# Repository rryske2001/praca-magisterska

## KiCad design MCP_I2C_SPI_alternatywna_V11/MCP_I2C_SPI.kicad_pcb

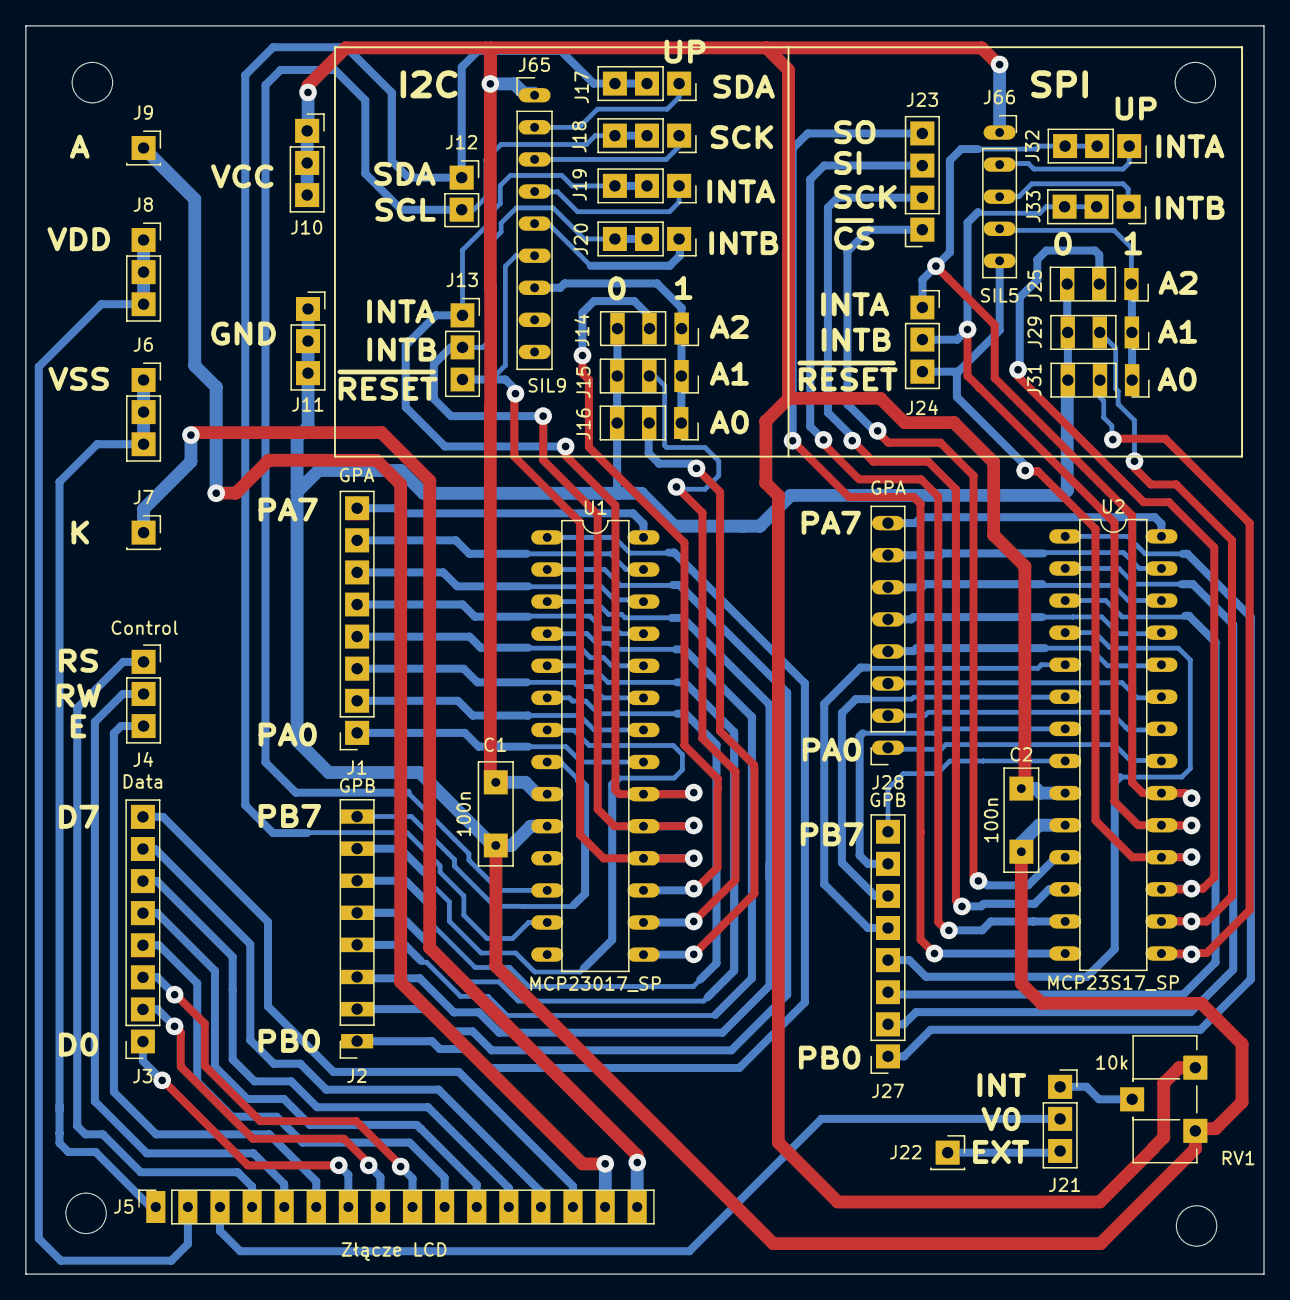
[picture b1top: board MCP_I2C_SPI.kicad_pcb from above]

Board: 2 copper layers, 98.0 x 98.8 mm, 38 parts (0 on the bottom side), 78 nets.

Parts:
C1, C2: 100n; C_Disc_D8.0mm_W2.5mm_P5.00mm_kwadart
J1, J28: GPA; PinSocket_1x08_P2.54mm_Vertical_kwadrat
J2, J27: GPB; PinSocket_1x08_P2.54mm_Vertical_kwadrat
J3: Data; PinSocket_1x08_P2.54mm_Vertical_kwadrat
J4: Control; PinSocket_1x03_P2.54mm_Vertical
J5: Złącze LCD; PinSocket_1x16_P2.54mm_Vertical_kwadrat
J6: VSS; PinSocket_1x03_P2.54mm_Vertical
J7: K; PinSocket_1x01_P2.54mm_Vertical_kwadart
J8: VDD; PinSocket_1x03_P2.54mm_Vertical
J9: A; PinSocket_1x01_P2.54mm_Vertical_kwadart
J10: VCC; PinSocket_1x03_P2.54mm_Vertical
J11: GND; PinSocket_1x03_P2.54mm_Vertical
J12: I2C; PinSocket_1x02_P2.54mm_Vertical_square
J13: Interrupt0; PinSocket_1x03_P2.54mm_Vertical
J14, J25: A2; PinSocket_1x03_P2.54mm_Vertical
J15, J29: A1; PinSocket_1x03_P2.54mm_Vertical
J16, J31: A0; PinSocket_1x03_P2.54mm_Vertical
J17: SDA; PinSocket_1x03_P2.54mm_Vertical
J18: SCK; PinSocket_1x03_P2.54mm_Vertical
J19, J32: INTA; PinSocket_1x03_P2.54mm_Vertical
J20, J33: INTB; PinSocket_1x03_P2.54mm_Vertical
J21: V0; PinSocket_1x03_P2.54mm_Vertical
J22: EXT; PinSocket_1x01_P2.54mm_Vertical_kwadart
J23: SPI; PinSocket_1x04_P2.54mm_Vertical
J24: InterruptS; PinSocket_1x03_P2.54mm_Vertical
J65: SIL9; PinHeader_1x09_P2.54mm_Vertical
J66: SIL5; PinSocket_1x05_P2.54mm_Vertical
RV1: 10k; Potentiometer_ACP_CA9-H5_Horizontal_kwadrat
U1: MCP23017_SP; DIP-28_W7.62mm
U2: MCP23S17_SP; DIP-28_W7.62mm

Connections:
+5V: C1.1, C2.1, J10.1, J10.2, J10.3, J65.1, J66.1, RV1.3, U1.9 (VDD), U2.9 (VDD)
CS: J23.1, U2.11 (~CS)
GND: C1.2, C2.2, J11.1, J11.2, J11.3, J14.3, J15.3, J16.3, J25.3, J29.3, J31.3, RV1.1, U1.10 (VSS), U2.10 (VSS)
INTA0: J13.1, J19.2, J19.3, U1.20 (INTA)
INTAS: J24.1, J32.2, J32.3, U2.20 (INTA)
INTB0: J13.2, J20.2, J20.3, U1.19 (INTB)
INTBS: J24.2, J33.2, J33.3, U2.19 (INTB)
unnamed: J1.1, U1.21 (GPA0)
unnamed: J1.2, U1.22 (GPA1)
unnamed: J1.3, U1.23 (GPA2)
unnamed: J1.4, U1.24 (GPA3)
unnamed: J1.5, U1.25 (GPA4)
unnamed: J1.6, U1.26 (GPA5)
unnamed: J1.7, U1.27 (GPA6)
unnamed: J1.8, U1.28 (GPA7)
unnamed: J2.1, U1.1 (GPB0)
unnamed: J2.2, U1.2 (GPB1)
unnamed: J2.3, U1.3 (GPB2)
unnamed: J2.4, U1.4 (GPB3)
unnamed: J2.5, U1.5 (GPB4)
unnamed: J2.6, U1.6 (GPB5)
unnamed: J2.7, U1.7 (GPB6)
unnamed: J2.8, U1.8 (GPB7)
unnamed: J3.1, J5.7
unnamed: J3.2, J5.8
unnamed: J3.3, J5.9
unnamed: J3.4, J5.10
unnamed: J3.5, J5.11
unnamed: J3.6, J5.12
unnamed: J3.7, J5.13
unnamed: J3.8, J5.14
unnamed: J4.1, J5.4
unnamed: J4.2, J5.5
unnamed: J4.3, J5.6
unnamed: J5.1, J6.1, J6.2, J6.3
unnamed: J5.2, J8.1, J8.2, J8.3
unnamed: J5.15, J9.1
unnamed: J5.16, J7.1
unnamed: J14.1, J15.1, J16.1, J65.7
unnamed: J14.2, U1.17 (A2)
unnamed: J15.2, U1.16 (A1)
unnamed: J16.2, U1.15 (A0)
unnamed: J17.1, J65.2
unnamed: J18.1, J65.3
unnamed: J19.1, J65.4
unnamed: J20.1, J65.5
unnamed: J21.1, RV1.2
unnamed: J5.3, J21.2
unnamed: J21.3, J22.1
unnamed: J25.1, J29.1, J31.1, J66.4
unnamed: J25.2, U2.17 (A2)
unnamed: J27.1, U2.1 (GPB0)
unnamed: J27.2, U2.2 (GPB1)
unnamed: J27.3, U2.3 (GPB2)
unnamed: J27.4, U2.4 (GPB3)
unnamed: J27.5, U2.5 (GPB4)
unnamed: J27.6, U2.6 (GPB5)
unnamed: J27.7, U2.7 (GPB6)
unnamed: J27.8, U2.8 (GPB7)
unnamed: J28.1, U2.21 (GPA0)
unnamed: J28.2, U2.22 (GPA1)
unnamed: J28.3, U2.23 (GPA2)
unnamed: J28.4, U2.24 (GPA3)
unnamed: J28.5, U2.25 (GPA4)
unnamed: J28.6, U2.26 (GPA5)
unnamed: J28.7, U2.27 (GPA6)
unnamed: J28.8, U2.28 (GPA7)
unnamed: J29.2, U2.16 (A1)
unnamed: J31.2, U2.15 (A0)
unnamed: J32.1, J66.2
unnamed: J33.1, J66.3
RESET0: J13.3, J65.6, U1.18 (~RESET)
RESETS: J24.3, J66.5, U2.18 (~RESET)
SCK: J23.2, U2.12 (SCK)
SCL: J12.2, J18.2, J18.3, U1.12 (SCK)
SDA: J12.1, J17.2, J17.3, U1.13 (SDA)
SI: J23.3, U2.13 (SI)
SO: J23.4, U2.14 (SO)

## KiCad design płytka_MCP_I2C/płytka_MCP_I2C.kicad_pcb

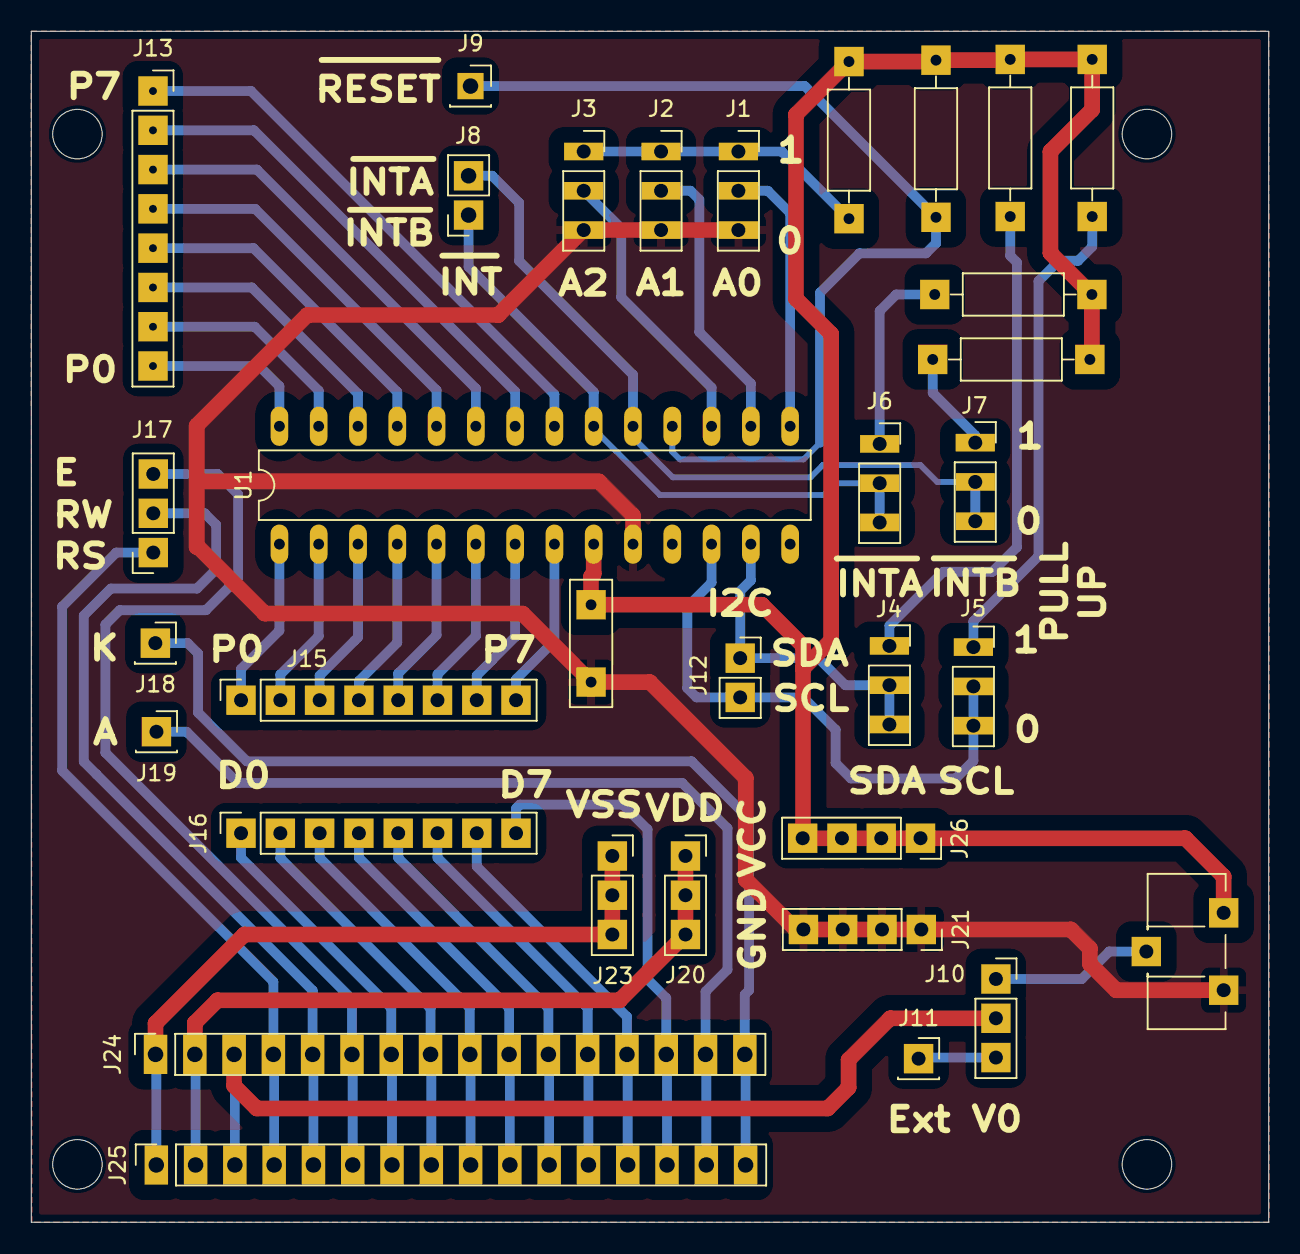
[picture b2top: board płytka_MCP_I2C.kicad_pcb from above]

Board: 2 copper layers, 80.0 x 77.0 mm, 33 parts (0 on the bottom side), 49 nets.

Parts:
C1: 47n; C_Disc_D8.0mm_W2.5mm_P5.00mm_kwadart
J1: A0; PinSocket_1x03_P2.54mm_Vertical
J2: A1; PinSocket_1x03_P2.54mm_Vertical
J3: A2; PinSocket_1x03_P2.54mm_Vertical
J4: SDA; PinSocket_1x03_P2.54mm_Vertical
J5: SCL; PinSocket_1x03_P2.54mm_Vertical
J6: INTA; PinSocket_1x03_P2.54mm_Vertical
J7: INTB; PinSocket_1x03_P2.54mm_Vertical
J8: INTA; PinSocket_1x02_P2.54mm_Vertical
J9: RESET; PinSocket_1x01_P2.54mm_Vertical
J10: V0; PinSocket_1x03_P2.54mm_Vertical
J11: Ext; PinSocket_1x01_P2.54mm_Vertical
J12: I2C; PinSocket_1x02_P2.54mm_Vertical
J13, J15: U2; PinSocket_1x08_P2.54mm_Vertical_kwadrat
J16: U3; PinSocket_1x08_P2.54mm_Vertical
J17: RS; PinSocket_1x03_P2.54mm_Vertical
J18: K; PinSocket_1x01_P2.54mm_Vertical_kwadart
J19: A; PinSocket_1x01_P2.54mm_Vertical_kwadart
J20: VDD; PinSocket_1x03_P2.54mm_Vertical
J21: GND; PinSocket_1x04_P2.54mm_Vertical
J23: VSS; PinSocket_1x03_P2.54mm_Vertical
J24: Conn_01x16_Pin; PinSocket_1x16_P2.54mm_Vertical_kwadrat
J25: LCD; PinSocket_1x16_P2.54mm_Vertical_kwadrat
J26: VCC; PinSocket_1x04_P2.54mm_Vertical
R1, R4, R5, R6: 10k; R_Axial_DIN0207_L6.3mm_D2.5mm_P10.16mm_Horizontal_square
R2, R3: 4.7k; R_Axial_DIN0207_L6.3mm_D2.5mm_P10.16mm_Horizontal_square
RV1: 10k; Potentiometer_ACP_CA9-H5_Horizontal_kwadrat
U1: MCP23017_SP; DIP-28_W7.62mm_LongPads_Edit

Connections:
GND: C1.1, J1.3, J2.3, J3.3, J21.1, J21.2, J21.3, J21.4, RV1.1, U1.10 (VSS)
unnamed: J1.1, J2.1, J3.1, R1.2
unnamed: J1.2, U1.15 (A0)
unnamed: J2.2, U1.16 (A1)
unnamed: J3.2, U1.17 (A2)
unnamed: J4.1, R2.2
unnamed: J5.1, R3.2
unnamed: J6.1, R4.2
unnamed: J6.2, J6.3, J8.1, U1.20 (INTA)
unnamed: J7.1, R5.2
unnamed: J7.2, J7.3, J8.2, U1.19 (INTB)
unnamed: J9.1, R6.1, U1.18 (~RESET)
unnamed: J10.1, RV1.2
unnamed: J10.2, J24.3, J25.3
unnamed: J10.3, J11.1
unnamed: J4.2, J4.3, J12.1, U1.13 (SDA)
unnamed: J5.2, J5.3, J12.2, U1.12 (SCK)
unnamed: J13.1, U1.21 (GPA0)
unnamed: J13.2, U1.22 (GPA1)
unnamed: J13.3, U1.23 (GPA2)
unnamed: J13.4, U1.24 (GPA3)
unnamed: J13.5, U1.25 (GPA4)
unnamed: J13.6, U1.26 (GPA5)
unnamed: J13.7, U1.27 (GPA6)
unnamed: J13.8, U1.28 (GPA7)
unnamed: J15.1, U1.1 (GPB0)
unnamed: J15.2, U1.2 (GPB1)
unnamed: J15.3, U1.3 (GPB2)
unnamed: J15.4, U1.4 (GPB3)
unnamed: J15.5, U1.5 (GPB4)
unnamed: J15.6, U1.6 (GPB5)
unnamed: J15.7, U1.7 (GPB6)
unnamed: J15.8, U1.8 (GPB7)
unnamed: J16.1, J24.7, J25.7
unnamed: J16.2, J24.8, J25.8
unnamed: J16.3, J24.9, J25.9
unnamed: J16.4, J24.10, J25.10
unnamed: J16.5, J24.11, J25.11
unnamed: J16.6, J24.12, J25.12
unnamed: J16.7, J24.13, J25.13
unnamed: J16.8, J24.14, J25.14
unnamed: J17.1, J24.4, J25.4
unnamed: J17.2, J24.5, J25.5
unnamed: J17.3, J24.6, J25.6
unnamed: J18.1, J24.16, J25.16
unnamed: J19.1, J24.15, J25.15
unnamed: J20.1, J20.2, J20.3, J24.2, J25.2
unnamed: J23.1, J23.2, J23.3, J24.1, J25.1
VCC: C1.2, J26.1, J26.2, J26.3, J26.4, R1.1, R2.1, R3.1, R4.1, R5.1, R6.2, RV1.3, U1.9 (VDD)

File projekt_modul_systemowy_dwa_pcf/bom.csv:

"Reference","Value","Datasheet","Footprint","Qty","DNP"
"C1,C2","47n","~","Library:C_Disc_D8.0mm_W2.5mm_P5.00mm_kwadart","2",""
"J1,J9","A0","~","Library:PinSocket_1x03_P2.54mm_Vertical","2",""
"J2,J8","A1","~","Library:PinSocket_1x03_P2.54mm_Vertical","2",""
"J3,J7","A2","~","Library:PinSocket_1x03_P2.54mm_Vertical","2",""
"J4","SDA","~","Library:PinSocket_1x03_P2.54mm_Vertical","1",""
"J5","SCL","~","Library:PinSocket_1x03_P2.54mm_Vertical","1",""
"J6,J13","INT","~","Connector_PinSocket_2.54mm:PinSocket_1x01_P2.54mm_Vertical,Library:PinSocket_1x03_P2.54mm_Vertical","2",""
"J10","V0","~","Library:PinSocket_1x03_P2.54mm_Vertical","1",""
"J11","Ext","~","Connector_PinSocket_2.54mm:PinSocket_1x01_P2.54mm_Vertical","1",""
"J12","I2C","~","Connector_PinSocket_2.54mm:PinSocket_1x02_P2.54mm_Vertical","1",""
"J14","U1","~","Library:PinSocket_1x03_P2.54mm_Vertical","1",""
"J15","U2","~","Library:PinSocket_1x08_P2.54mm_Vertical_kwadrat","1",""
"J16","U3","~","Connector_PinSocket_2.54mm:PinSocket_1x08_P2.54mm_Vertical","1",""
"J17","RS","~","Connector_PinSocket_2.54mm:PinSocket_1x03_P2.54mm_Vertical","1",""
"J18","K","~","Library:PinSocket_1x01_P2.54mm_Vertical_kwadart","1",""
"J19","A","~","Library:PinSocket_1x01_P2.54mm_Vertical_kwadart","1",""
"J20","VDD","~","Connector_PinSocket_2.54mm:PinSocket_1x03_P2.54mm_Vertical","1",""
"J21","GND","~","Connector_PinSocket_2.54mm:PinSocket_1x04_P2.54mm_Vertical","1",""
"J23","VSS","~","Connector_PinSocket_2.54mm:PinSocket_1x03_P2.54mm_Vertical","1",""
"J24","Conn_01x16_Pin","~","Library:PinSocket_1x16_P2.54mm_Vertical_kwadrat","1",""
"J25","LCD","~","Library:PinSocket_1x16_P2.54mm_Vertical_kwadrat","1",""
"J26","VCC","~","Connector_PinSocket_2.54mm:PinSocket_1x04_P2.54mm_Vertical","1",""
"R1,R4,R5,RV1","10k","~","Library:Potentiometer_ACP_CA9-H5_Horizontal_kwadrat,Library:R_Axial_DIN0207_L6.3mm_D2.5mm_P10.16mm_Horizontal_square","4",""
"R2,R3","4.7k","~","Library:R_Axial_DIN0207_L6.3mm_D2.5mm_P10.16mm_Horizontal_square","2",""
"U1,U2","PCF8574","http://www.nxp.com/docs/en/data-sheet/PCF8574_PCF8574A.pdf","Library:DIP-16_W7.62mm_Socket_LongPads_lezki","2",""

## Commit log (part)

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2026-03-02 Pierwszy commit
2026-03-03 Pomiary dla I2C
2026-03-21 Pierwsze przymiarki do plytki
2026-03-22 Dodano płytkę z dwoma PCF
2026-03-22 MCP I2C wersja 1.0
2026-03-23 Kosmetyczne zmiany, wydruk schematu, oraz plytki do pdf
2026-03-23 Dodany pin RESET
2026-03-23 Wersja 2 plytki I2C
2026-03-23 MCP_SPI płytka wersja 1.0
2026-03-23 _MCP_I2C płytka do zmniejszenia
2026-03-24 Korekcja rozmiaru płytki, utworzenie draftow, do druku
2026-03-24 Normalizacja wielkosci plytke
2026-03-24 Zaktualizowane pomiary
2026-03-25 Wyrownane otwory
2026-03-25 Zmieniono otwory na rezystory oraz kondensotry 0,7mm
2026-03-25 Zwiekszenie otworow na 0.7 mm dla SPI i I2C
2026-04-14 Dodane rysunki
2026-04-17 Kolejne rysunki
2026-04-29 Dodanie plytkek z wersja na frezowanie
2026-05-09 Dodany kod na wskaznik 7-segm dla PCF8574
2026-05-27 Nowe programy testowe
2026-05-29 Dodałem zdjęcia z oscyloskopu
2026-05-30 Dodałem pomiary do SPI
2026-06-01 Plytka SPI_I2C
2026-06-01 Płytka MCP in progress
2026-06-02 Płytka MCP_I2C_SPIv1 gotowa
2026-06-03 Poprawki płytki MCP_I2C_SPI V1
2026-06-09 I2C_SPI_PCB_V2
2026-06-10 I2C_SPI_V2_fix
2026-06-12 Zmiana footprintu rezystorow - 6mm
2026-06-13 Update PCB MCP_I2C_SPI V3
2026-06-17 płytka MCP 17.06.2026
2026-06-19 PCB MCP_I2C_SPI_V4
2026-06-19 kolejna wersja MCP
2026-06-19 MCP_I2C_SPI_V5
2026-06-22 MCP_I2C_SPI_PCB_V6
2026-06-23 Płytka MCP_I2C_SPI_V7
2026-06-23 obudowa do modułu PCF
2026-06-23 MCP_I2C_SPI PCB V8
2026-06-23 MCP_I2C_SPI PCB V9
2026-06-24 MCP_I2C_SPI PCB V11
2026-06-25 MCP_I2C_SPI PCB V12
2026-06-28 Final verison MCP_I2C_SPI, ready to order
